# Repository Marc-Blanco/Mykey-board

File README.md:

## MyKey Board (mikey board)

I tried to make a functional and cool midi keyboard like a piano with 88 keys DIY, with cool features. It has 2 speakers and 2 rotary encoders to tingle things, I would like to improve on the project and this is kind of a Deltarune reference so maybe add easter eggs?

Photos:

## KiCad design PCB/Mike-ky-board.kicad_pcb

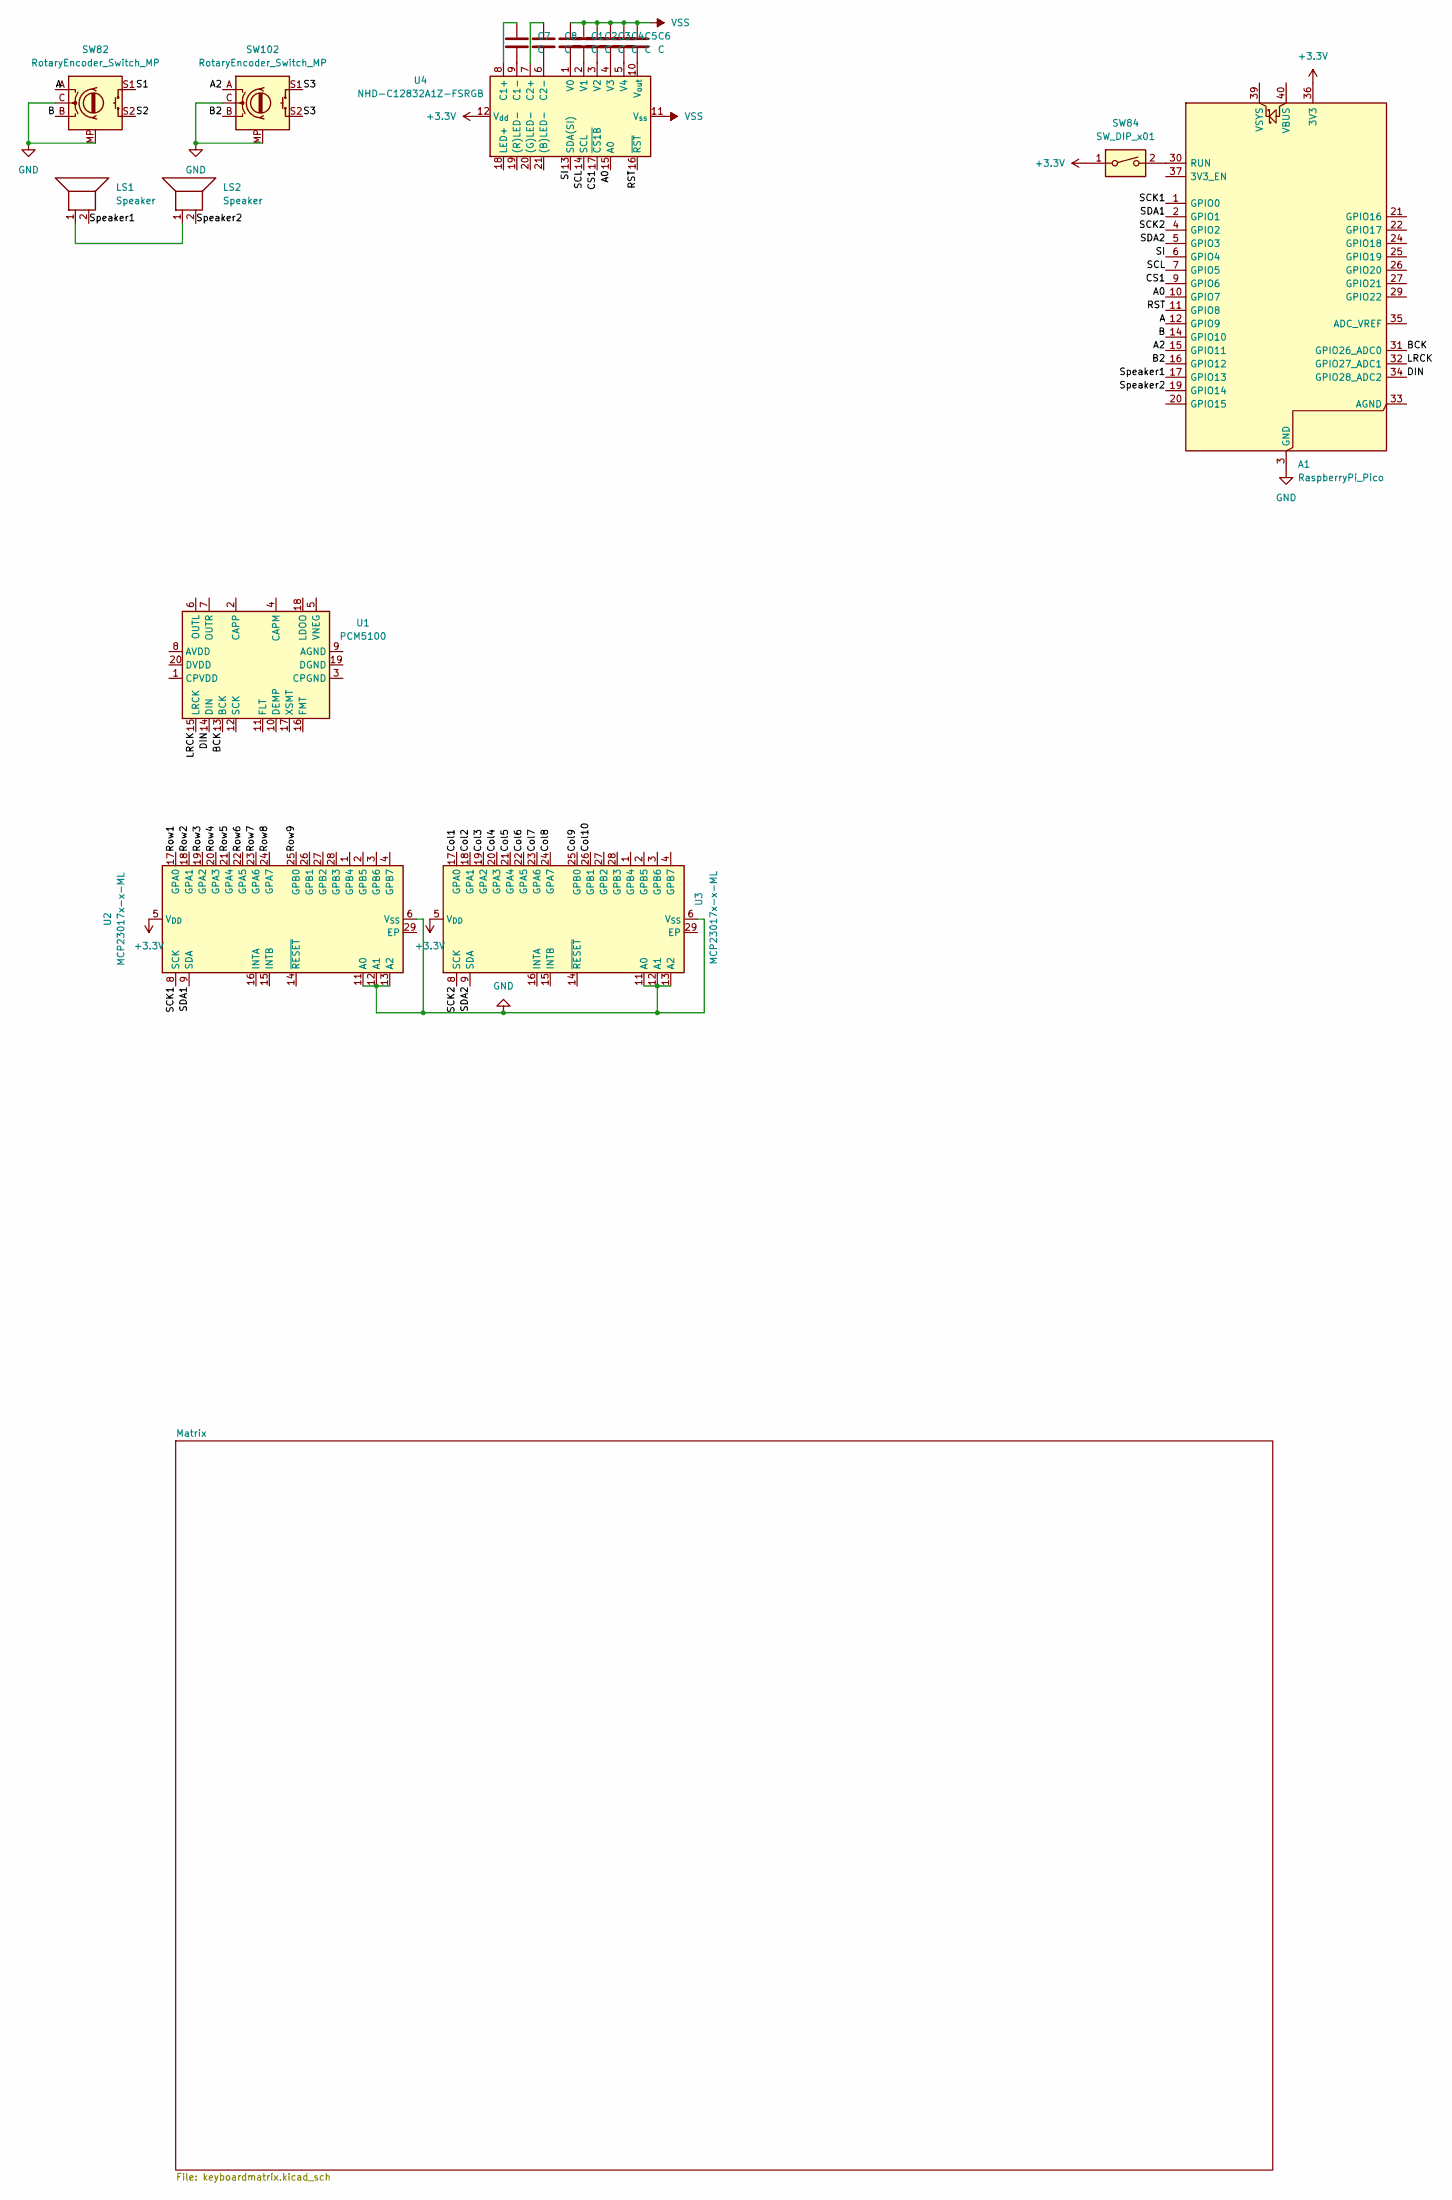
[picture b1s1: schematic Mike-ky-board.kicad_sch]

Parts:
A1: RaspberryPi_Pico; RaspberryPi_Pico_Common_Unspecified
C1, C2, C3, C4, C5, C6, C7, C8: C
LS1, LS2: Speaker; Speaker_CUI_CMR-1206S-67
SW82, SW102: RotaryEncoder_Switch_MP; RotaryEncoder_Alps_EC11E-Switch_Vertical_H20mm
SW84: SW_DIP_x01; SW_PUSH_1P1T_6x3.5mm_H4.3_APEM_MJTP1243
U1: PCM5100; TSSOP-20_4.4x6.5mm_P0.65mm
U2, U3: MCP23017x-x-ML; QFN-28-1EP_6x6mm_P0.65mm_EP4.25x4.25mm
U4: NHD-C12832A1Z-FSRGB

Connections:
+3.3V: A1.36 (3V3), SW84.1, U2.5 (V_{DD}), U3.5 (V_{DD}), U4.12 (V_{dd})
/A: A1.12 (GPIO9), SW82.A
/A0: A1.10 (GPIO7), U4.15 (A0)
/A2: A1.15 (GPIO11), SW102.A
/B: A1.14 (GPIO10), SW82.B
/B2: A1.16 (GPIO12), SW102.B
/BCK: A1.31 (GPIO26_ADC0), U1.13 (BCK)
/CS1: A1.9 (GPIO6), U4.17 (~CS1B)
/Col1: U3.17 (GPA0)
/Col2: U3.18 (GPA1)
/Col3: U3.19 (GPA2)
/Col4: U3.20 (GPA3)
/Col5: U3.21 (GPA4)
/Col6: U3.22 (GPA5)
/Col7: U3.23 (GPA6)
/Col8: U3.24 (GPA7)
/Col9: U3.25 (GPB0)
/Col10: U3.26 (GPB1)
/DIN: A1.34 (GPIO28_ADC2), U1.14 (DIN)
/LRCK: A1.32 (GPIO27_ADC1), U1.15 (LRCK)
/RST: A1.11 (GPIO8), U4.16 (~RST)
/Row1: U2.17 (GPA0)
/Row2: U2.18 (GPA1)
/Row3: U2.19 (GPA2)
/Row4: U2.20 (GPA3)
/Row5: U2.21 (GPA4)
/Row6: U2.22 (GPA5)
/Row7: U2.23 (GPA6)
/Row8: U2.24 (GPA7)
/Row9: U2.25 (GPB0)
/S1: SW82.S1
/S2: SW82.S2
/S3: SW102.S1, SW102.S2
/SCK1: A1.1 (GPIO0), U2.8 (SCK)
/SCK2: A1.4 (GPIO2), U3.8 (SCK)
/SCL: A1.7 (GPIO5), U4.14 (SCL)
/SDA1: A1.2 (GPIO1), U2.9 (SDA)
/SDA2: A1.5 (GPIO3), U3.9 (SDA)
/SI: A1.6 (GPIO4), U4.13 (SDA(SI))
/Speaker1: A1.17 (GPIO13), LS1.2
/Speaker2: A1.19 (GPIO14), LS2.2
GND: A1.3 (GND), A1.8 (GND), A1.13 (GND), A1.18 (GND), A1.23 (GND), A1.28 (GND), A1.38 (GND), SW82.C, SW82.MP, SW102.C, SW102.MP, U2.6 (V_{SS}), U2.11 (A0), U2.12 (A1), U2.13 (A2), U3.6 (V_{SS}), U3.11 (A0), U3.12 (A1), U3.13 (A2)
unnamed: A1.30 (RUN), SW84.2
unnamed: LS1.1, LS2.1
unnamed: C7.1, U4.8 (C1+)
unnamed: C7.2, U4.9 (C1-)
unnamed: C8.1, U4.7 (C2+)
unnamed: C8.2, U4.6 (C2-)
unnamed: C1.2, U4.1 (V0)
unnamed: C2.2, U4.2 (V1)
unnamed: C3.2, U4.3 (V2)
unnamed: C4.2, U4.4 (V3)
unnamed: C5.2, U4.5 (V4)
unnamed: C6.2, U4.10 (V_{out})
VSS: C1.1, C2.1, C3.1, C4.1, C5.1, C6.1, U4.11 (V_{ss})

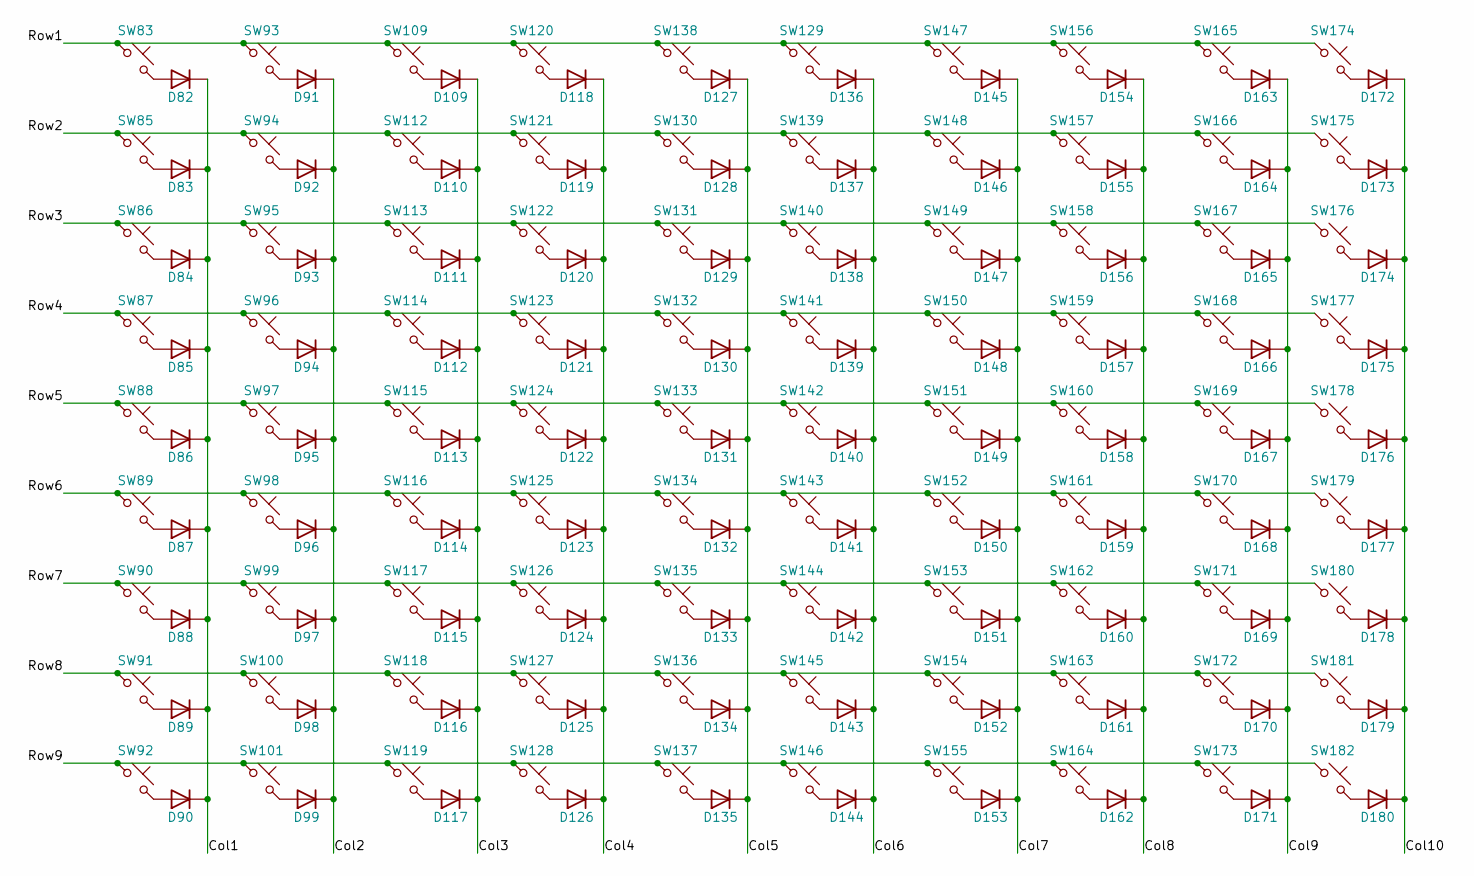
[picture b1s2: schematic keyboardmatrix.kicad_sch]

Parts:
D82, D83, D84, D85, D86, D87, D88, D89, D90, D91, D92, D93, D94, D95, D96, D97, D98, D99, D109, D110, D111, D112, D113, D114, D115, D116, D117, D118, D119, D120, D121, D122, D123, D124, D125, D126, D127, D128, D129, D130, D131, D132, D133, D134, D135, D136, D137, D138, D139, D140, D141, D142, D143, D144, D145, D146, D147, D148, D149, D150, D151, D152, D153, D154, D155, D156, D157, D158, D159, D160, D161, D162, D163, D164, D165, D166, D167, D168, D169, D170, D171, D172, D173, D174, D175, D176, D177, D178, D179, D180: 1N914; D_DO-35_SOD27_P7.62mm_Horizontal
SW83, SW85, SW86, SW87, SW88, SW89, SW90, SW91, SW92, SW93, SW94, SW95, SW96, SW97, SW98, SW99, SW100, SW101, SW109, SW112, SW113, SW114, SW115, SW116, SW117, SW118, SW119, SW120, SW121, SW122, SW123, SW124, SW125, SW126, SW127, SW128, SW129, SW130, SW131, SW132, SW133, SW134, SW135, SW136, SW137, SW138, SW139, SW140, SW141, SW142, SW143, SW144, SW145, SW146, SW147, SW148, SW149, SW150, SW151, SW152, SW153, SW154, SW155, SW156, SW157, SW158, SW159, SW160, SW161, SW162, SW163, SW164, SW165, SW166, SW167, SW168, SW169, SW170, SW171, SW172, SW173, SW174, SW175, SW176, SW177, SW178, SW179, SW180: SW_Push_45deg; SW_DIP_SPSTx01_Piano_10.8x4.1mm_W7.62mm_P2.54mm
SW181, SW182: SW_Push_45deg; SW_Tactile_Straight_KSA0Axx1LFTR

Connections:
/Matrix/Col1: D82.1 (K), D83.1 (K), D84.1 (K), D85.1 (K), D86.1 (K), D87.1 (K), D88.1 (K), D89.1 (K), D90.1 (K)
/Matrix/Col2: D91.1 (K), D92.1 (K), D93.1 (K), D94.1 (K), D95.1 (K), D96.1 (K), D97.1 (K), D98.1 (K), D99.1 (K)
/Matrix/Col3: D109.1 (K), D110.1 (K), D111.1 (K), D112.1 (K), D113.1 (K), D114.1 (K), D115.1 (K), D116.1 (K), D117.1 (K)
/Matrix/Col4: D118.1 (K), D119.1 (K), D120.1 (K), D121.1 (K), D122.1 (K), D123.1 (K), D124.1 (K), D125.1 (K), D126.1 (K)
/Matrix/Col5: D127.1 (K), D128.1 (K), D129.1 (K), D130.1 (K), D131.1 (K), D132.1 (K), D133.1 (K), D134.1 (K), D135.1 (K)
/Matrix/Col6: D136.1 (K), D137.1 (K), D138.1 (K), D139.1 (K), D140.1 (K), D141.1 (K), D142.1 (K), D143.1 (K), D144.1 (K)
/Matrix/Col7: D145.1 (K), D146.1 (K), D147.1 (K), D148.1 (K), D149.1 (K), D150.1 (K), D151.1 (K), D152.1 (K), D153.1 (K)
/Matrix/Col8: D154.1 (K), D155.1 (K), D156.1 (K), D157.1 (K), D158.1 (K), D159.1 (K), D160.1 (K), D161.1 (K), D162.1 (K)
/Matrix/Col9: D163.1 (K), D164.1 (K), D165.1 (K), D166.1 (K), D167.1 (K), D168.1 (K), D169.1 (K), D170.1 (K), D171.1 (K)
/Matrix/Col10: D172.1 (K), D173.1 (K), D174.1 (K), D175.1 (K), D176.1 (K), D177.1 (K), D178.1 (K), D179.1 (K), D180.1 (K)
/Matrix/Row1: SW83.1, SW93.1, SW109.1, SW120.1, SW129.1, SW138.1, SW147.1, SW156.1, SW165.1, SW174.1
/Matrix/Row2: SW85.1, SW94.1, SW112.1, SW121.1, SW130.1, SW139.1, SW148.1, SW157.1, SW166.1, SW175.1
/Matrix/Row3: SW86.1, SW95.1, SW113.1, SW122.1, SW131.1, SW140.1, SW149.1, SW158.1, SW167.1, SW176.1
/Matrix/Row4: SW87.1, SW96.1, SW114.1, SW123.1, SW132.1, SW141.1, SW150.1, SW159.1, SW168.1, SW177.1
/Matrix/Row5: SW88.1, SW97.1, SW115.1, SW124.1, SW133.1, SW142.1, SW151.1, SW160.1, SW169.1, SW178.1
/Matrix/Row6: SW89.1, SW98.1, SW116.1, SW125.1, SW134.1, SW143.1, SW152.1, SW161.1, SW170.1, SW179.1
/Matrix/Row7: SW90.1, SW99.1, SW117.1, SW126.1, SW135.1, SW144.1, SW153.1, SW162.1, SW171.1, SW180.1
/Matrix/Row8: SW91.1, SW100.1, SW118.1, SW127.1, SW136.1, SW145.1, SW154.1, SW163.1, SW172.1, SW181.1
/Matrix/Row9: SW92.1, SW101.1, SW119.1, SW128.1, SW137.1, SW146.1, SW155.1, SW164.1, SW173.1, SW182.1
unnamed: D82.2 (A), SW83.2
unnamed: D83.2 (A), SW85.2
unnamed: D84.2 (A), SW86.2
unnamed: D85.2 (A), SW87.2
unnamed: D86.2 (A), SW88.2
unnamed: D87.2 (A), SW89.2
unnamed: D88.2 (A), SW90.2
unnamed: D89.2 (A), SW91.2
unnamed: D90.2 (A), SW92.2
unnamed: D91.2 (A), SW93.2
unnamed: D92.2 (A), SW94.2
unnamed: D93.2 (A), SW95.2
unnamed: D94.2 (A), SW96.2
unnamed: D95.2 (A), SW97.2
unnamed: D96.2 (A), SW98.2
unnamed: D97.2 (A), SW99.2
unnamed: D98.2 (A), SW100.2
unnamed: D99.2 (A), SW101.2
unnamed: D109.2 (A), SW109.2
unnamed: D110.2 (A), SW112.2
unnamed: D111.2 (A), SW113.2
unnamed: D112.2 (A), SW114.2
unnamed: D113.2 (A), SW115.2
unnamed: D114.2 (A), SW116.2
unnamed: D115.2 (A), SW117.2
unnamed: D116.2 (A), SW118.2
unnamed: D117.2 (A), SW119.2
unnamed: D118.2 (A), SW120.2
unnamed: D119.2 (A), SW121.2
unnamed: D120.2 (A), SW122.2
unnamed: D121.2 (A), SW123.2
unnamed: D122.2 (A), SW124.2
unnamed: D123.2 (A), SW125.2
unnamed: D124.2 (A), SW126.2
unnamed: D125.2 (A), SW127.2
unnamed: D126.2 (A), SW128.2
unnamed: D127.2 (A), SW138.2
unnamed: D128.2 (A), SW130.2
unnamed: D129.2 (A), SW131.2
unnamed: D130.2 (A), SW132.2
unnamed: D131.2 (A), SW133.2
unnamed: D132.2 (A), SW134.2
unnamed: D133.2 (A), SW135.2
unnamed: D134.2 (A), SW136.2
unnamed: D135.2 (A), SW137.2
unnamed: D136.2 (A), SW129.2
unnamed: D137.2 (A), SW139.2
unnamed: D138.2 (A), SW140.2
unnamed: D139.2 (A), SW141.2
unnamed: D140.2 (A), SW142.2
unnamed: D141.2 (A), SW143.2
unnamed: D142.2 (A), SW144.2
unnamed: D143.2 (A), SW145.2
unnamed: D144.2 (A), SW146.2
unnamed: D145.2 (A), SW147.2
unnamed: D146.2 (A), SW148.2
unnamed: D147.2 (A), SW149.2
unnamed: D148.2 (A), SW150.2
unnamed: D149.2 (A), SW151.2
unnamed: D150.2 (A), SW152.2
unnamed: D151.2 (A), SW153.2
unnamed: D152.2 (A), SW154.2
unnamed: D153.2 (A), SW155.2
unnamed: D154.2 (A), SW156.2
unnamed: D155.2 (A), SW157.2
unnamed: D156.2 (A), SW158.2
unnamed: D157.2 (A), SW159.2
unnamed: D158.2 (A), SW160.2
unnamed: D159.2 (A), SW161.2
unnamed: D160.2 (A), SW162.2
unnamed: D161.2 (A), SW163.2
unnamed: D162.2 (A), SW164.2
unnamed: D163.2 (A), SW165.2
unnamed: D164.2 (A), SW166.2
unnamed: D165.2 (A), SW167.2
unnamed: D166.2 (A), SW168.2
unnamed: D167.2 (A), SW169.2
unnamed: D168.2 (A), SW170.2
unnamed: D169.2 (A), SW171.2
unnamed: D170.2 (A), SW172.2
unnamed: D171.2 (A), SW173.2
unnamed: D172.2 (A), SW174.2
unnamed: D173.2 (A), SW175.2
unnamed: D174.2 (A), SW176.2
unnamed: D175.2 (A), SW177.2
unnamed: D176.2 (A), SW178.2
unnamed: D177.2 (A), SW179.2
unnamed: D178.2 (A), SW180.2
unnamed: D179.2 (A), SW181.2
unnamed: D180.2 (A), SW182.2

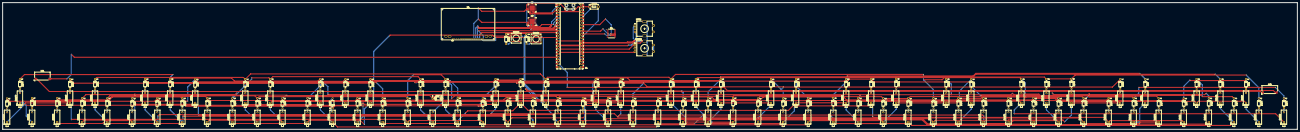
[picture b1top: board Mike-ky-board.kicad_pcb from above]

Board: 2 copper layers, 1008.5 x 98.7 mm, 190 parts (0 on the bottom side), 132 nets.
